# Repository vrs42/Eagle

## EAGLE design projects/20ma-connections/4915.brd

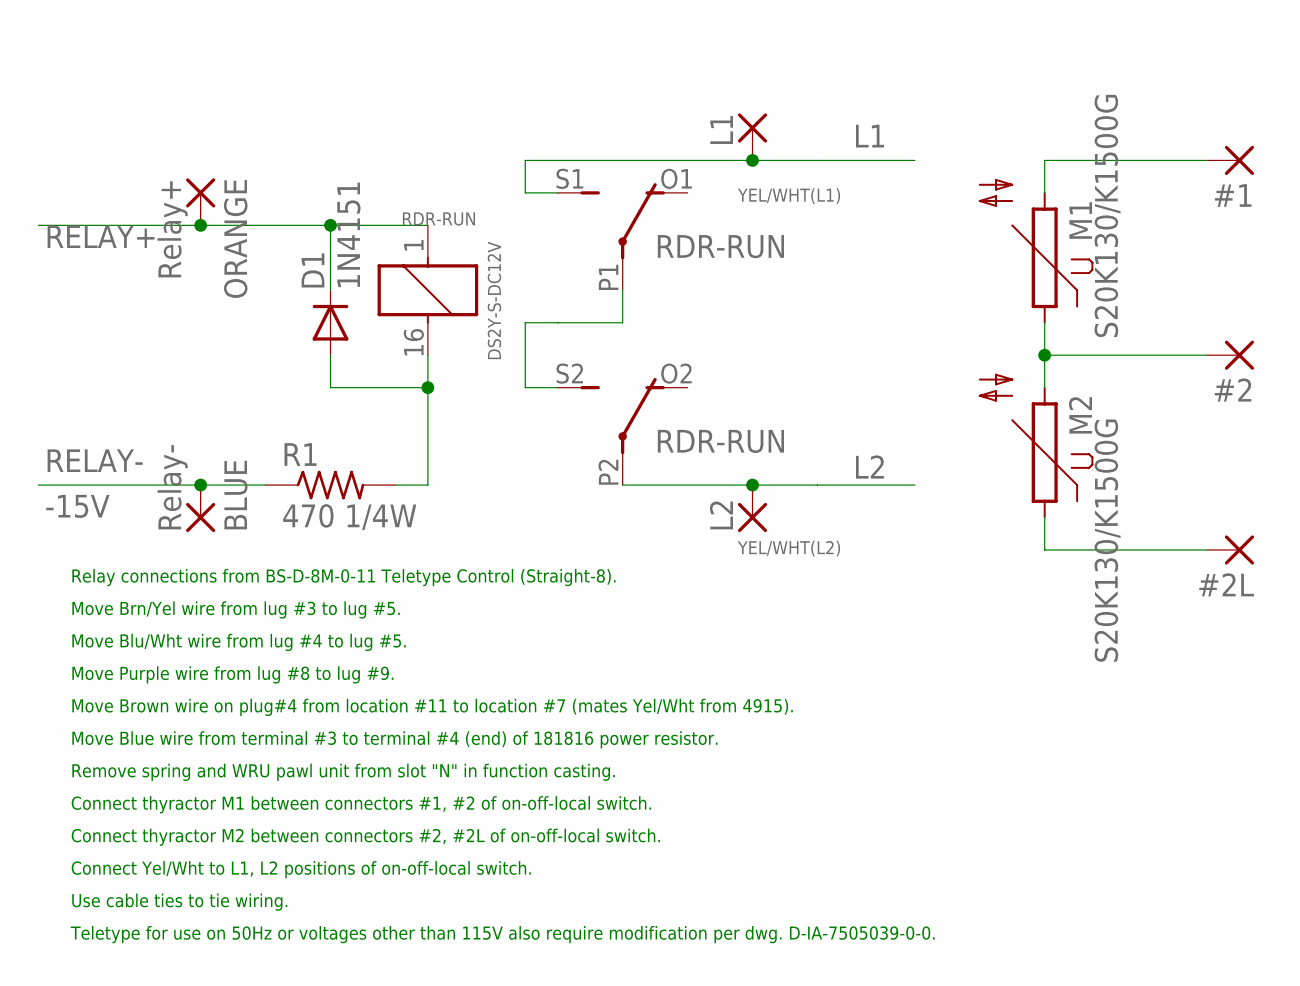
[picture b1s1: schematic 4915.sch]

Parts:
#1, #2, #2L: 2,15/1,0
BLUE: Relay-; 2,15/1,0
D1: 1N4151; DO35-10
M1, M2: S20K130/K1500G; S10K40
ORANGE: Relay+; 2,15/1,0
R1: 470 1/4W; 0309/12
RDR-RUN: DS2Y-S-DC12V; 351
YEL/WHT(L1): L1; 2,15/1,0
YEL/WHT(L2): L2; 2,15/1,0

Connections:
-15V: BLUE.1, R1.1
L1: RDR-RUN.S1 (S), YEL/WHT(L1).1
L2: RDR-RUN.P2, YEL/WHT(L2).1
unnamed: D1.A, R1.2, RDR-RUN.16 (2)
unnamed: RDR-RUN.P1, RDR-RUN.S2 (S)
unnamed: #1.1, M1.2
unnamed: #2.1, M1.1, M2.2
unnamed: #2L.1, M2.1
RELAY+: D1.C, ORANGE.1, RDR-RUN.1

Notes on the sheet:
RELAY-
Relay connections from BS-D-8M-0-11 Teletype Control (Straight-8).
Move Brown wire on plug#4 from location #11 to location #7 (mates Yel/Wht from 4915).
Move Brn/Yel wire from lug #3 to lug #5.
Move Blu/Wht wire from lug #4 to lug #5.
Move Purple wire from lug #8 to lug #9.
Move Blue wire from terminal #3 to terminal #4 (end) of 181816 power resistor.
Connect thyractor M2 between connectors #2, #2L of on-off-local switch.
Connect thyractor M1 between connectors #1, #2 of on-off-local switch.
Remove spring and WRU pawl unit from slot "N" in function casting.
Connect Yel/Wht to L1, L2 positions of on-off-local switch.
Use cable ties to tie wiring.
Teletype for use on 50Hz or voltages other than 115V also require modification per dwg. D-IA-7505039-0-0.

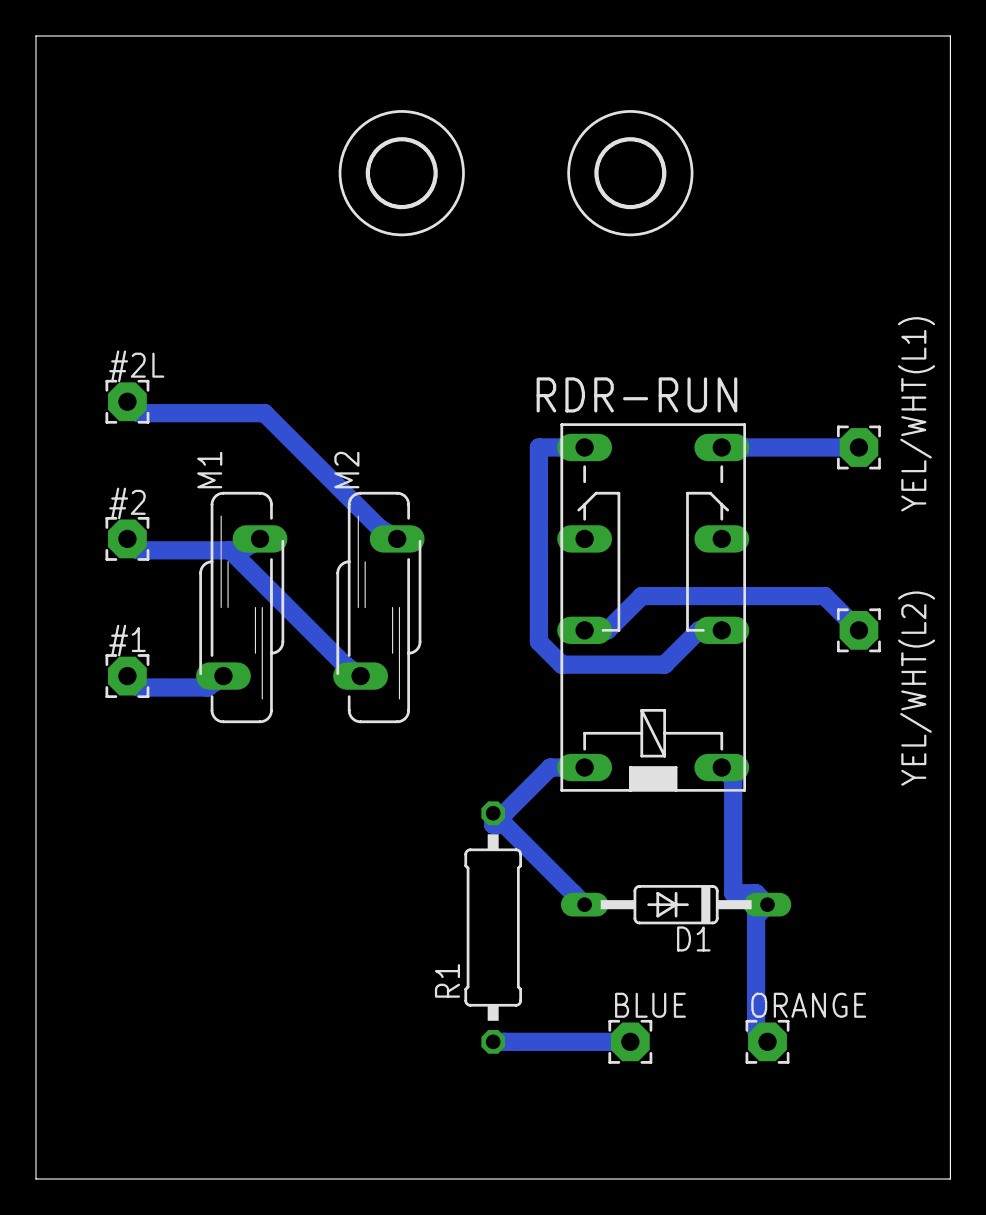
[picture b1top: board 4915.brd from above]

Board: 2 copper layers, 50.8 x 63.5 mm, 14 parts (0 on the bottom side), 9 nets.

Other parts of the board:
U$1, U$2: 3,6

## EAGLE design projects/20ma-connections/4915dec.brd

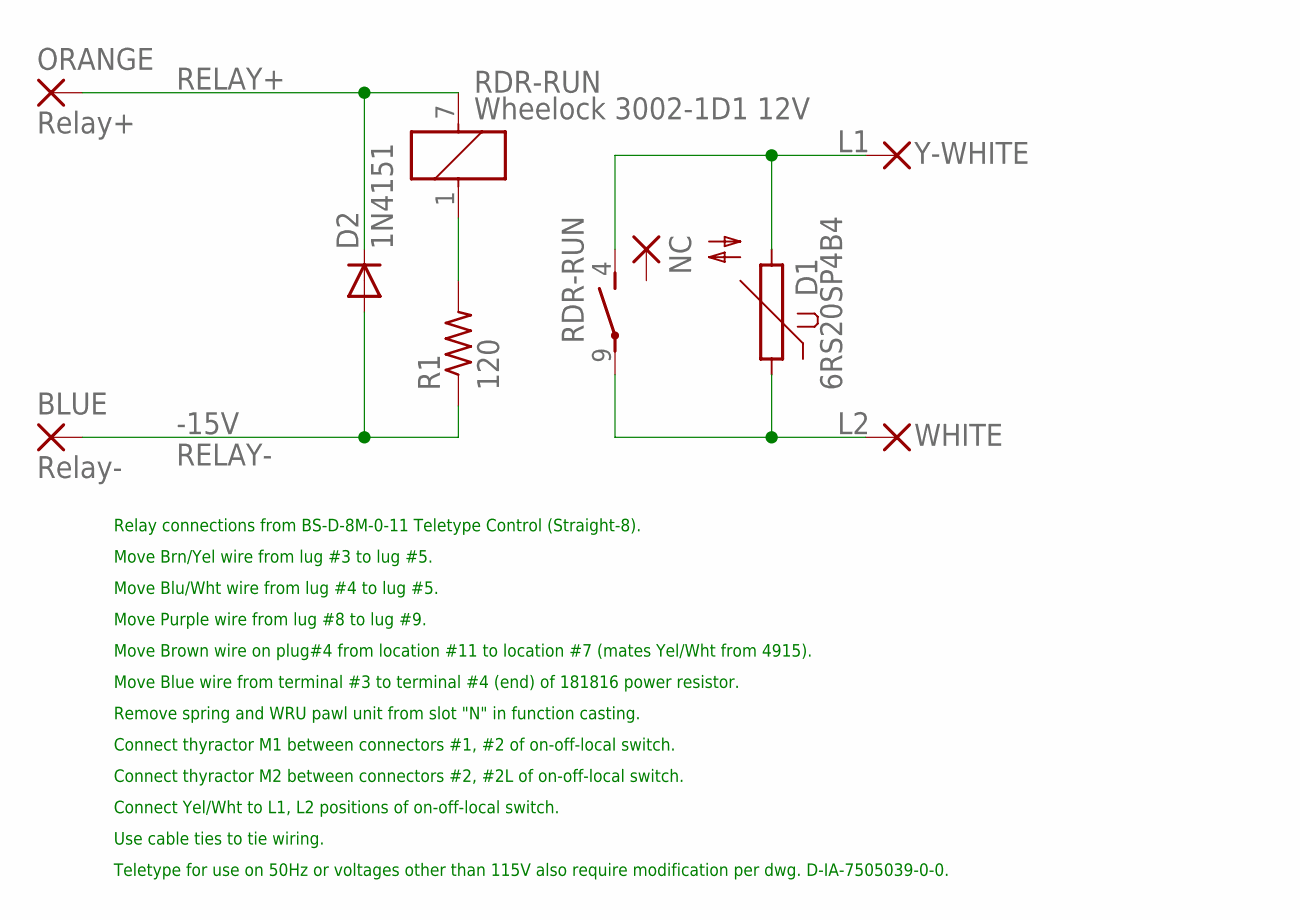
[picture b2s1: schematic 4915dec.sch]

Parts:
BLUE: Relay-; 3,17/1,3
D1: 6RS20SP4B4
D2: 1N4151; DO35-10
NC: 3,17/1,3
ORANGE: Relay+; 3,17/1,3
R1: 120; 0207/10
RDR-RUN: Wheelock 3002-1D1 12V; 3002-1D1
WHITE: L2; 3,17/1,3
Y-WHITE: L1; 3,17/1,3

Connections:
-15V: BLUE.1, D2.A, R1.1
L1: D1.2, RDR-RUN.4, Y-WHITE.1
L2: D1.1, RDR-RUN.9, WHITE.1
unnamed: R1.2, RDR-RUN.1
RELAY+: D2.C, ORANGE.1, RDR-RUN.7

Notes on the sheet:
RELAY-
Relay connections from BS-D-8M-0-11 Teletype Control (Straight-8).
Move Brown wire on plug#4 from location #11 to location #7 (mates Yel/Wht from 4915).
Move Brn/Yel wire from lug #3 to lug #5.
Move Blu/Wht wire from lug #4 to lug #5.
Move Purple wire from lug #8 to lug #9.
Move Blue wire from terminal #3 to terminal #4 (end) of 181816 power resistor.
Connect thyractor M2 between connectors #2, #2L of on-off-local switch.
Connect thyractor M1 between connectors #1, #2 of on-off-local switch.
Remove spring and WRU pawl unit from slot "N" in function casting.
Connect Yel/Wht to L1, L2 positions of on-off-local switch.
Use cable ties to tie wiring.
Teletype for use on 50Hz or voltages other than 115V also require modification per dwg. D-IA-7505039-0-0.

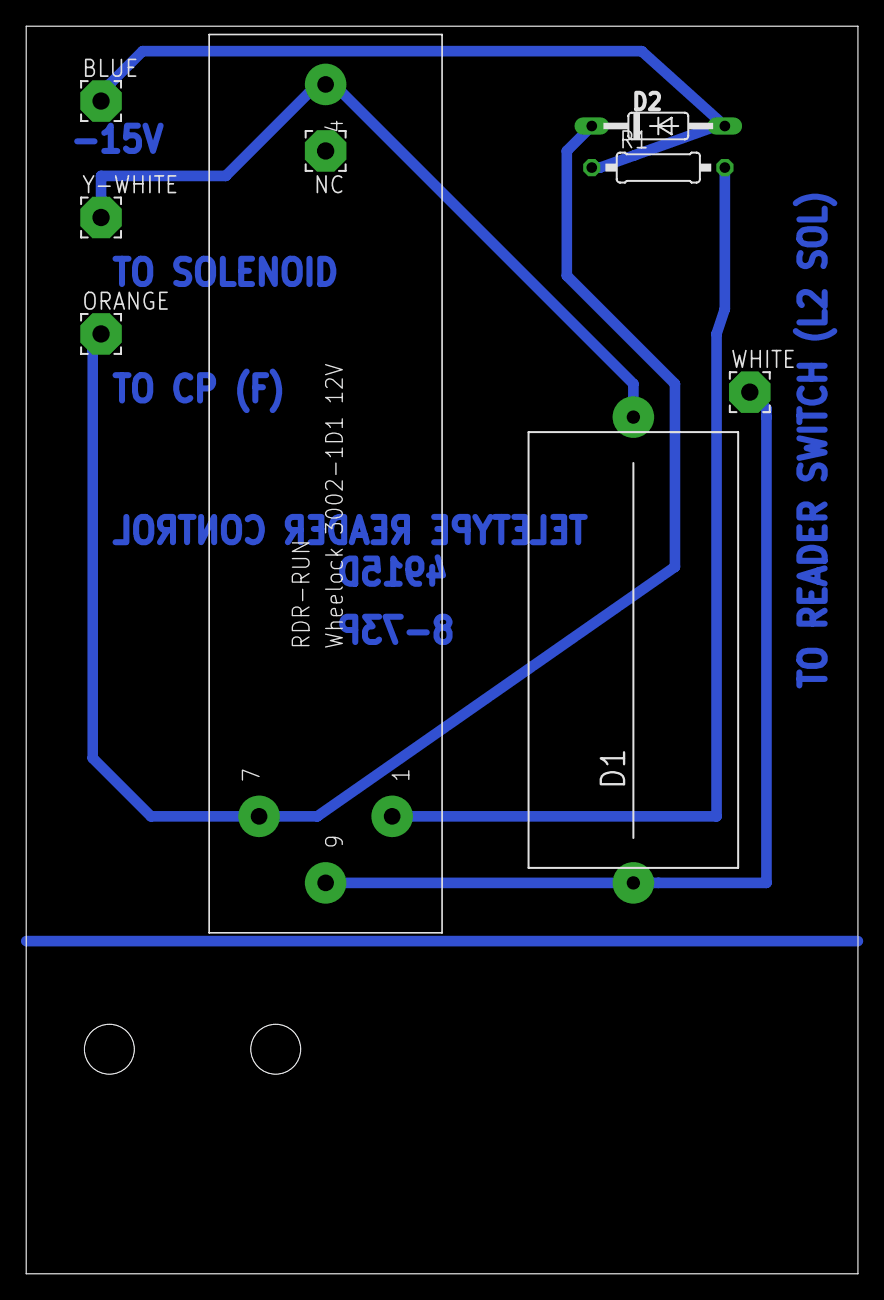
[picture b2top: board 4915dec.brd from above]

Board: 2 copper layers, 63.5 x 95.2 mm, 9 parts (0 on the bottom side), 5 nets.

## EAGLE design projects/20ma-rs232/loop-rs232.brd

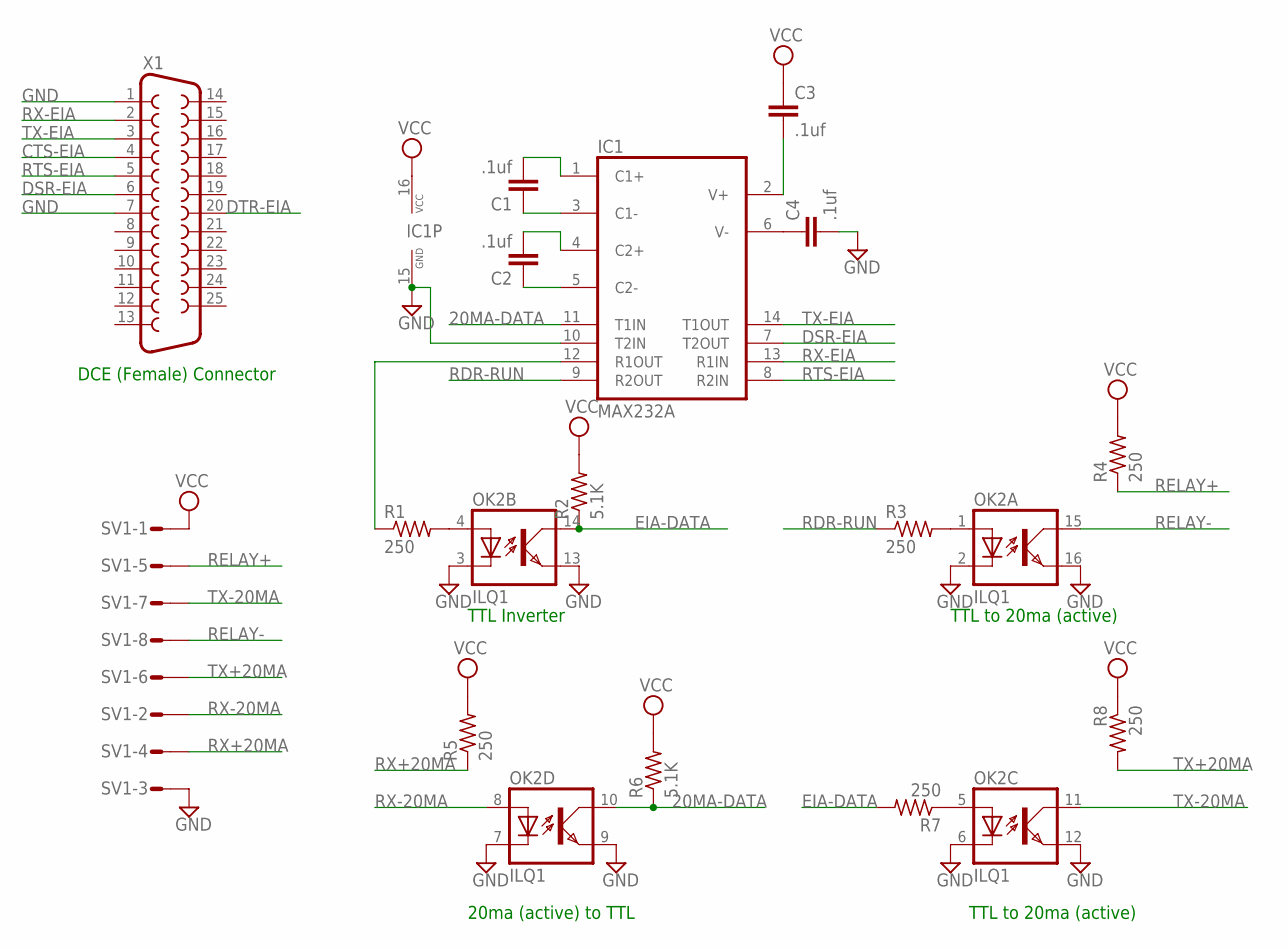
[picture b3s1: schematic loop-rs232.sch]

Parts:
C1, C2, C3, C4: .1uf; C050-025X075
IC1: MAX232A; DIL16
OK2: ILQ1; DIL16
R1, R3, R4, R5, R7, R8: 250; 0207/10
R2, R6: 5.1K; 0207/10
SV1: S08P
X1: F25H

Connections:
20MA-DATA: IC1.11 (T1IN), OK2.10 (COL), R6.1
CTS-EIA: X1.4
DSR-EIA: IC1.7 (T2OUT), X1.6
DTR-EIA: X1.20
EIA-DATA: OK2.14 (COL), R2.1, R7.2
GND: C4.2, IC1.10 (T2IN), IC1.15 (GND), OK2.2 (C), OK2.3 (C), OK2.6 (C), OK2.7 (C), OK2.9 (EMIT), OK2.12 (EMIT), OK2.13 (EMIT), OK2.16 (EMIT), SV1.3, X1.1, X1.7
unnamed: C2.1, IC1.5 (C2-)
unnamed: C2.2, IC1.4 (C2+)
unnamed: C1.2, IC1.1 (C1+)
unnamed: C1.1, IC1.3 (C1-)
unnamed: IC1.12 (R1OUT), R1.1
unnamed: C3.2, IC1.2 (V+)
unnamed: C4.1, IC1.6 (V-)
unnamed: OK2.4 (A), R1.2
unnamed: OK2.1 (A), R3.2
unnamed: OK2.5 (A), R7.1
RDR-RUN: IC1.9 (R2OUT), R3.1
RELAY+: R4.1, SV1.5
RELAY-: OK2.15 (COL), SV1.8
RTS-EIA: IC1.8 (R2IN), X1.5
RX+20MA: R5.1, SV1.4
RX-20MA: OK2.8 (A), SV1.2
RX-EIA: IC1.13 (R1IN), X1.2
TX+20MA: R8.2, SV1.6
TX-20MA: OK2.11 (COL), SV1.7
TX-EIA: IC1.14 (T1OUT), X1.3
VCC: C3.1, IC1.16 (VCC), R2.2, R4.2, R5.2, R6.2, R8.1, SV1.1

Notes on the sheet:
TTL to 20ma (active)
20ma (active) to TTL
TTL Inverter
DCE (Female) Connector

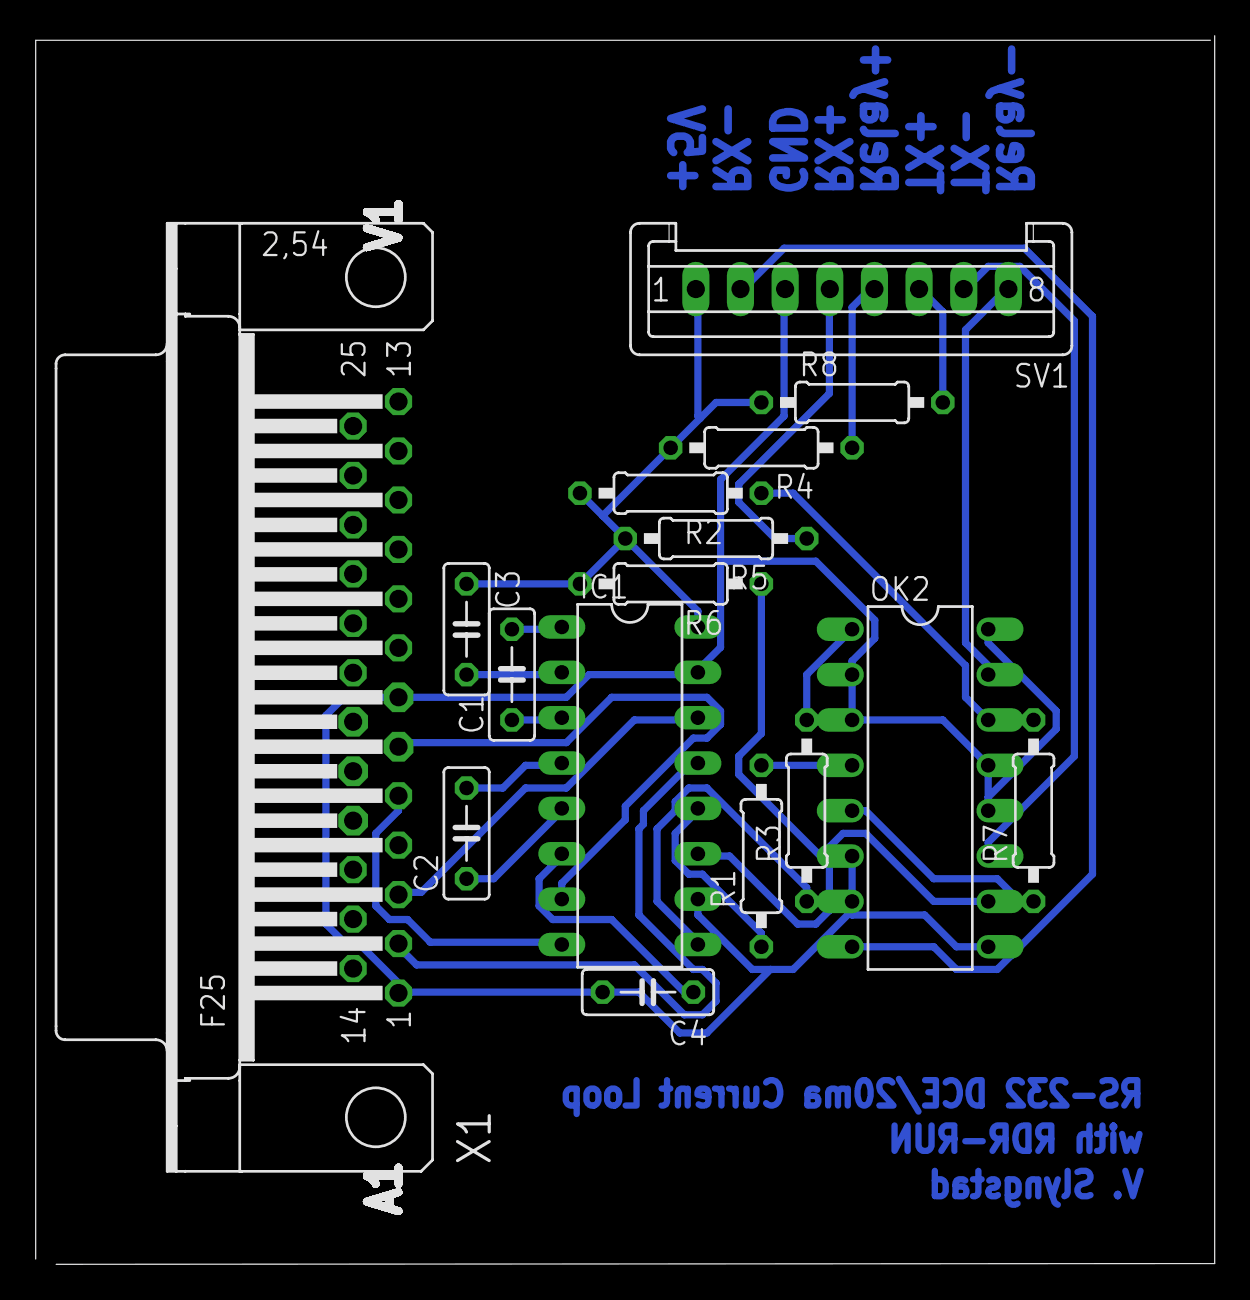
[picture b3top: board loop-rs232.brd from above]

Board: 2 copper layers, 66.0 x 68.8 mm, 16 parts (0 on the bottom side), 25 nets.

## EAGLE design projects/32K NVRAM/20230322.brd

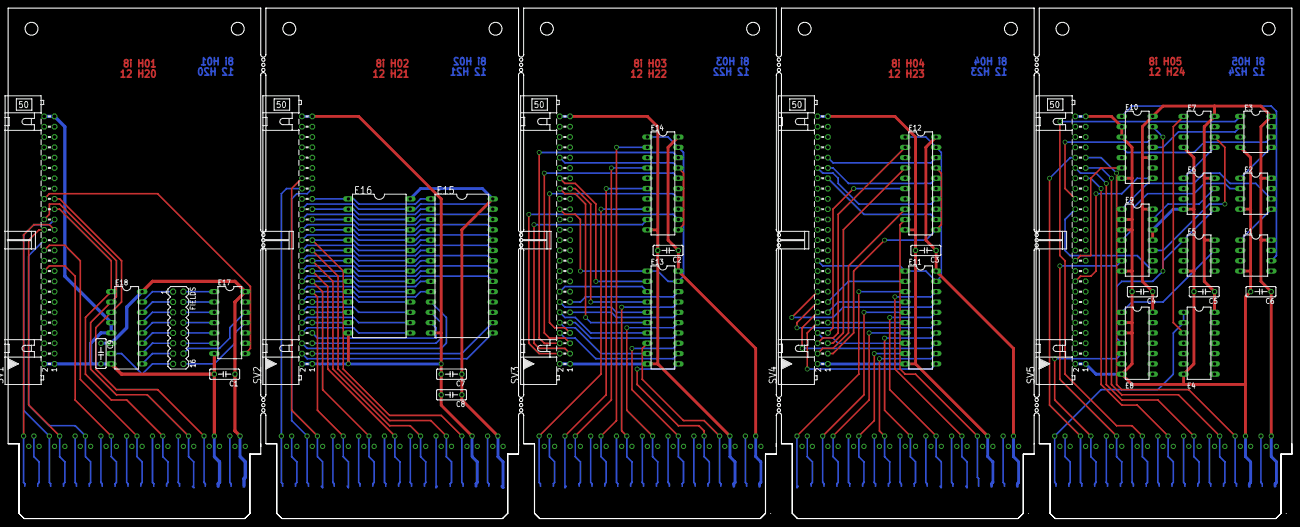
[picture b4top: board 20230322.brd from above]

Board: 2 copper layers, 316.2 x 125.7 mm, 44 parts (0 on the bottom side), 128 nets.

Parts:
C1, C2, C3, C4, C5, C6, C7, C8, C9: 0.1uF; C050-025X075
E1, E2, E3, E5, E6, E7: MXD1000; DIL08
E4: 74LS00N; DIL14
E8, E9, E10: 74LS74N; DIL14
E11, E12: 74S244N; DIL20
E13, E14: 74S240N; DIL20
E15, E16: DS1230; DIL28-6
E17: 74LS30N; DIL14
E18: 74LS138N; DIL16
FIELDS: 7 6 5 4 3 2 1 0; MA08-2
H01, H02, H03, H04, H05: EDGE-CON1
SV1, SV2, SV3, SV4, SV5: ML50L
U$1, U$2, U$3, U$4, U$5: THRU-HOLE2; THRU-HOLEB
U$6: DECPROTO11111

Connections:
BMA00(1): E15.23, E16.23, H01.K2, SV1.24, SV2.24, U$1.K2
BMA01(1): E15.21, E16.21, H01.M2, SV1.20, SV2.20, U$1.M2
BMA02(1): E15.24, E16.24, H01.P2, SV1.26, SV2.26, U$1.P2
BMA03(1): E15.25, E16.25, H01.S2, SV1.28, SV2.28, U$1.S2
BMA04(1): E15.3, E16.3, H01.T2, SV1.29, SV2.29, U$1.T2
BMA05(1): E15.4, E16.4, H01.V2, SV1.27, SV2.27, U$1.V2
BMA06(1): E15.5, E16.5, H02.D2, SV2.25, U$2.D2
BMA07(1): E15.6, E16.6, H02.E2, SV2.23, U$2.E2
BMA08(1): E15.7, E16.7, H02.H2, SV2.21, U$2.H2
BMA09(1): E15.8, E16.8, H02.K2, SV2.19, U$2.K2
BMA10(1): E15.9, E16.9, H02.M2, SV2.17, U$2.M2
BMA11(1): E15.10, E16.10, H02.P2, SV2.15, U$2.P2
BTP2(0): E4.3, E7.1
BTP2(1): E4.1, E4.2, H05.V2, U$5.V2
CS(0): E10.8, E15.20, E16.20, SV2.18, SV5.18
D0: E11.2, E13.18, E16.11, SV2.13, SV3.13, SV4.13
D1: E11.4, E13.16, E16.12, SV2.11, SV3.11, SV4.11
D2: E11.6, E13.14, E16.13, SV2.9, SV3.9, SV4.9
D3: E11.8, E13.12, E16.15, SV2.8, SV3.8, SV4.8
D4: E11.11, E13.9, E16.16, SV2.10, SV3.10, SV4.10
D5: E11.13, E13.7, E16.17, SV2.12, SV3.12, SV4.12
D6: E11.15, E13.5, E16.18, SV2.14, SV3.14, SV4.14
D7: E11.17, E13.3, E16.19, SV2.16, SV3.16, SV4.16
D8: E12.2, E14.18, E15.11, SV2.6, SV3.6, SV4.6
D9: E12.4, E14.16, E15.12, SV2.5, SV3.5, SV4.5
D10: E12.6, E14.14, E15.13, SV2.7, SV3.7, SV4.7
D11: E12.8, E14.12, E15.15, SV2.4, SV3.4, SV4.4
EA0(1): E15.1, E16.1, E18.3, H01.D2, SV1.33, SV2.33, U$1.D2
EA1(1): E15.26, E16.26, E18.2, H01.E2, SV1.30, SV2.30, U$1.E2
EA2(1): E15.2, E16.2, E18.1, H01.H2, SV1.31, SV2.31, U$1.H2
FS(1): E10.12, E17.8, SV1.34, SV5.34
GND: C1.2, C2.2, C3.2, C4.2, C5.2, C6.2, C7.2, C8.2, C9.2, E1.4, E2.4, E3.4, E4.7, E5.4, E6.4, E7.4, E8.2, E8.3, E8.7, E9.2, E9.3, E9.7, E9.11, E9.12, E10.2, E10.3, E10.7, E11.10, E12.10, E13.10, E14.10, E15.14, E16.14, E17.7, E18.4, E18.5, E18.8, H01.C2, H02.C2, H03.C2, H04.C2, H05.C2, SV1.1, SV1.2, SV1.49, SV1.50, SV2.1, SV2.2, SV2.49, SV2.50, SV3.1, SV3.2, SV3.49, SV3.50, SV4.1, SV4.2, SV4.49, SV4.50, SV5.1, SV5.2, SV5.49, SV5.50, U$1.C2, U$2.C2, U$3.C2, U$4.C2, U$5.C2
MBODD_P: E14.11, E14.13, E14.15, E14.17, H05.T2, SV3.42, SV5.42, U$5.T2
MCBMB00(0): E13.2, H02.S2, SV2.38, SV3.38, U$2.S2
MCBMB01(0): E13.4, H02.T2, SV2.35, SV3.35, U$2.T2
MCBMB02(0): E13.6, H02.V2, SV2.36, SV3.36, U$2.V2
MCBMB03(0): E13.8, H03.D2, U$3.D2
MCBMB04(0): E13.11, H03.E2, U$3.E2
MCBMB05(0): E13.13, H03.H2, U$3.H2
MCBMB06(0): E13.15, H03.K2, U$3.K2
MCBMB07(0): E13.17, H03.M2, U$3.M2
MCBMB08(0): E14.2, H03.P2, U$3.P2
MCBMB09(0): E14.4, H03.S2, U$3.S2
MCBMB10(0): E14.6, H03.T2, U$3.T2
MCBMB11(0): E14.8, H03.V2, U$3.V2
MEM00: E11.18, H04.E2, U$4.E2
MEM01: E11.16, H04.H2, U$4.H2
MEM02: E11.14, H04.K2, U$4.K2
MEM03: E11.12, H04.M2, U$4.M2
MEM04: E11.9, H04.P2, U$4.P2
MEM05: E11.7, H04.S2, U$4.S2
MEM06: E11.5, H04.T2, U$4.T2
MEM07: E11.3, H04.V2, U$4.V2
MEM08: E12.18, H05.D2, SV4.41, SV5.41, U$5.D2
MEM09: E12.16, H05.E2, SV4.39, SV5.39, U$5.E2
MEM10: E12.14, H05.H2, SV4.40, SV5.40, U$5.H2
MEM11: E12.12, H05.K2, SV4.37, SV5.37, U$5.K2
MEMDONE(1): E8.5, H05.S2, U$5.S2
MEMSTART(0): E3.1, H05.M2, U$5.M2
MEM_P: E12.9, H04.D2, U$4.D2
MS100: E3.2, E10.11
MS150: E3.6, E10.4
MS250: E2.1, E3.5
MS350: E2.2, E9.4
MS400: E2.6, E9.1
MS500: E1.1, E2.5
MS650: E1.6, E10.1
unnamed: H01.L2, U$1.L2
unnamed: H01.N2, U$1.N2
unnamed: H01.R2, U$1.R2
unnamed: H02.L2, U$2.L2
unnamed: H02.N2, U$2.N2
unnamed: H01.J2, U$1.J2
unnamed: H02.R2, U$2.R2
unnamed: H01.F2, U$1.F2
unnamed: H02.J2, U$2.J2
unnamed: H02.F2, U$2.F2
unnamed: H02.U2, U$2.U2
unnamed: H01.U2, U$1.U2
unnamed: H02.B2, U$2.B2
unnamed: H01.B2, U$1.B2
unnamed: E18.15, FIELDS.1
unnamed: E18.14, FIELDS.3
unnamed: E18.13, FIELDS.5
unnamed: E18.12, FIELDS.7
unnamed: E18.11, FIELDS.9
unnamed: E18.10, FIELDS.11
unnamed: E18.9, FIELDS.13
unnamed: E18.7, FIELDS.15
unnamed: E17.4, FIELDS.8
unnamed: E17.3, FIELDS.6
unnamed: E17.2, FIELDS.4
unnamed: E17.1, FIELDS.2
unnamed: E17.5, FIELDS.10
unnamed: E17.6, FIELDS.12
unnamed: E17.12, FIELDS.14
unnamed: E17.11, FIELDS.16
unnamed: H04.J2, U$4.J2
unnamed: H04.L2, U$4.L2
unnamed: H04.N2, U$4.N2
unnamed: H03.J2, U$3.J2
unnamed: H03.L2, U$3.L2
unnamed: H03.N2, U$3.N2
unnamed: H03.F2, U$3.F2
unnamed: H03.R2, U$3.R2
unnamed: H03.B2, U$3.B2
unnamed: H03.U2, U$3.U2
unnamed: H05.J2, U$5.J2
unnamed: H05.L2, U$5.L2
unnamed: H05.N2, U$5.N2
unnamed: H05.F2, U$5.F2
unnamed: H05.R2, U$5.R2
unnamed: H05.B2, U$5.B2
unnamed: H05.U2, U$5.U2
unnamed: H04.F2, U$4.F2
unnamed: H04.R2, U$4.R2
unnamed: H04.B2, U$4.B2
unnamed: H04.U2, U$4.U2
OE(0): E10.6, E11.1, E11.19, E12.1, E12.19, E15.22, E16.22, SV2.22, SV4.22, SV5.22
PARITY: E12.11, E12.13, E12.15, E12.17, E14.9, E15.16, SV2.3, SV3.3, SV4.3
STROBE(0): E9.6, H05.P2, U$5.P2
TP150: E7.6, E9.10
TP250: E6.1, E7.5
TP300: E6.7, E9.13
TP500: E5.1, E6.5, E8.4, E10.13
TP550: E5.7, E8.1
VCC: C1.1, C2.1, C3.1, C4.1, C5.1, C6.1, C7.1, C8.1, C9.1, E1.8, E2.8, E3.8, E4.14, E5.8, E6.8, E7.8, E8.14, E9.14, E10.10, E10.14, E11.20, E12.20, E13.20, E14.20, E15.28, E16.28, E17.14, E18.6, E18.16, H01.A2, H02.A2, H03.A2, H04.A2, H05.A2, U$1.A2, U$2.A2, U$3.A2, U$4.A2, U$5.A2
WE(0): E9.8, E13.1, E13.19, E14.1, E14.19, E15.27, E16.27, SV2.32, SV3.32, SV5.32

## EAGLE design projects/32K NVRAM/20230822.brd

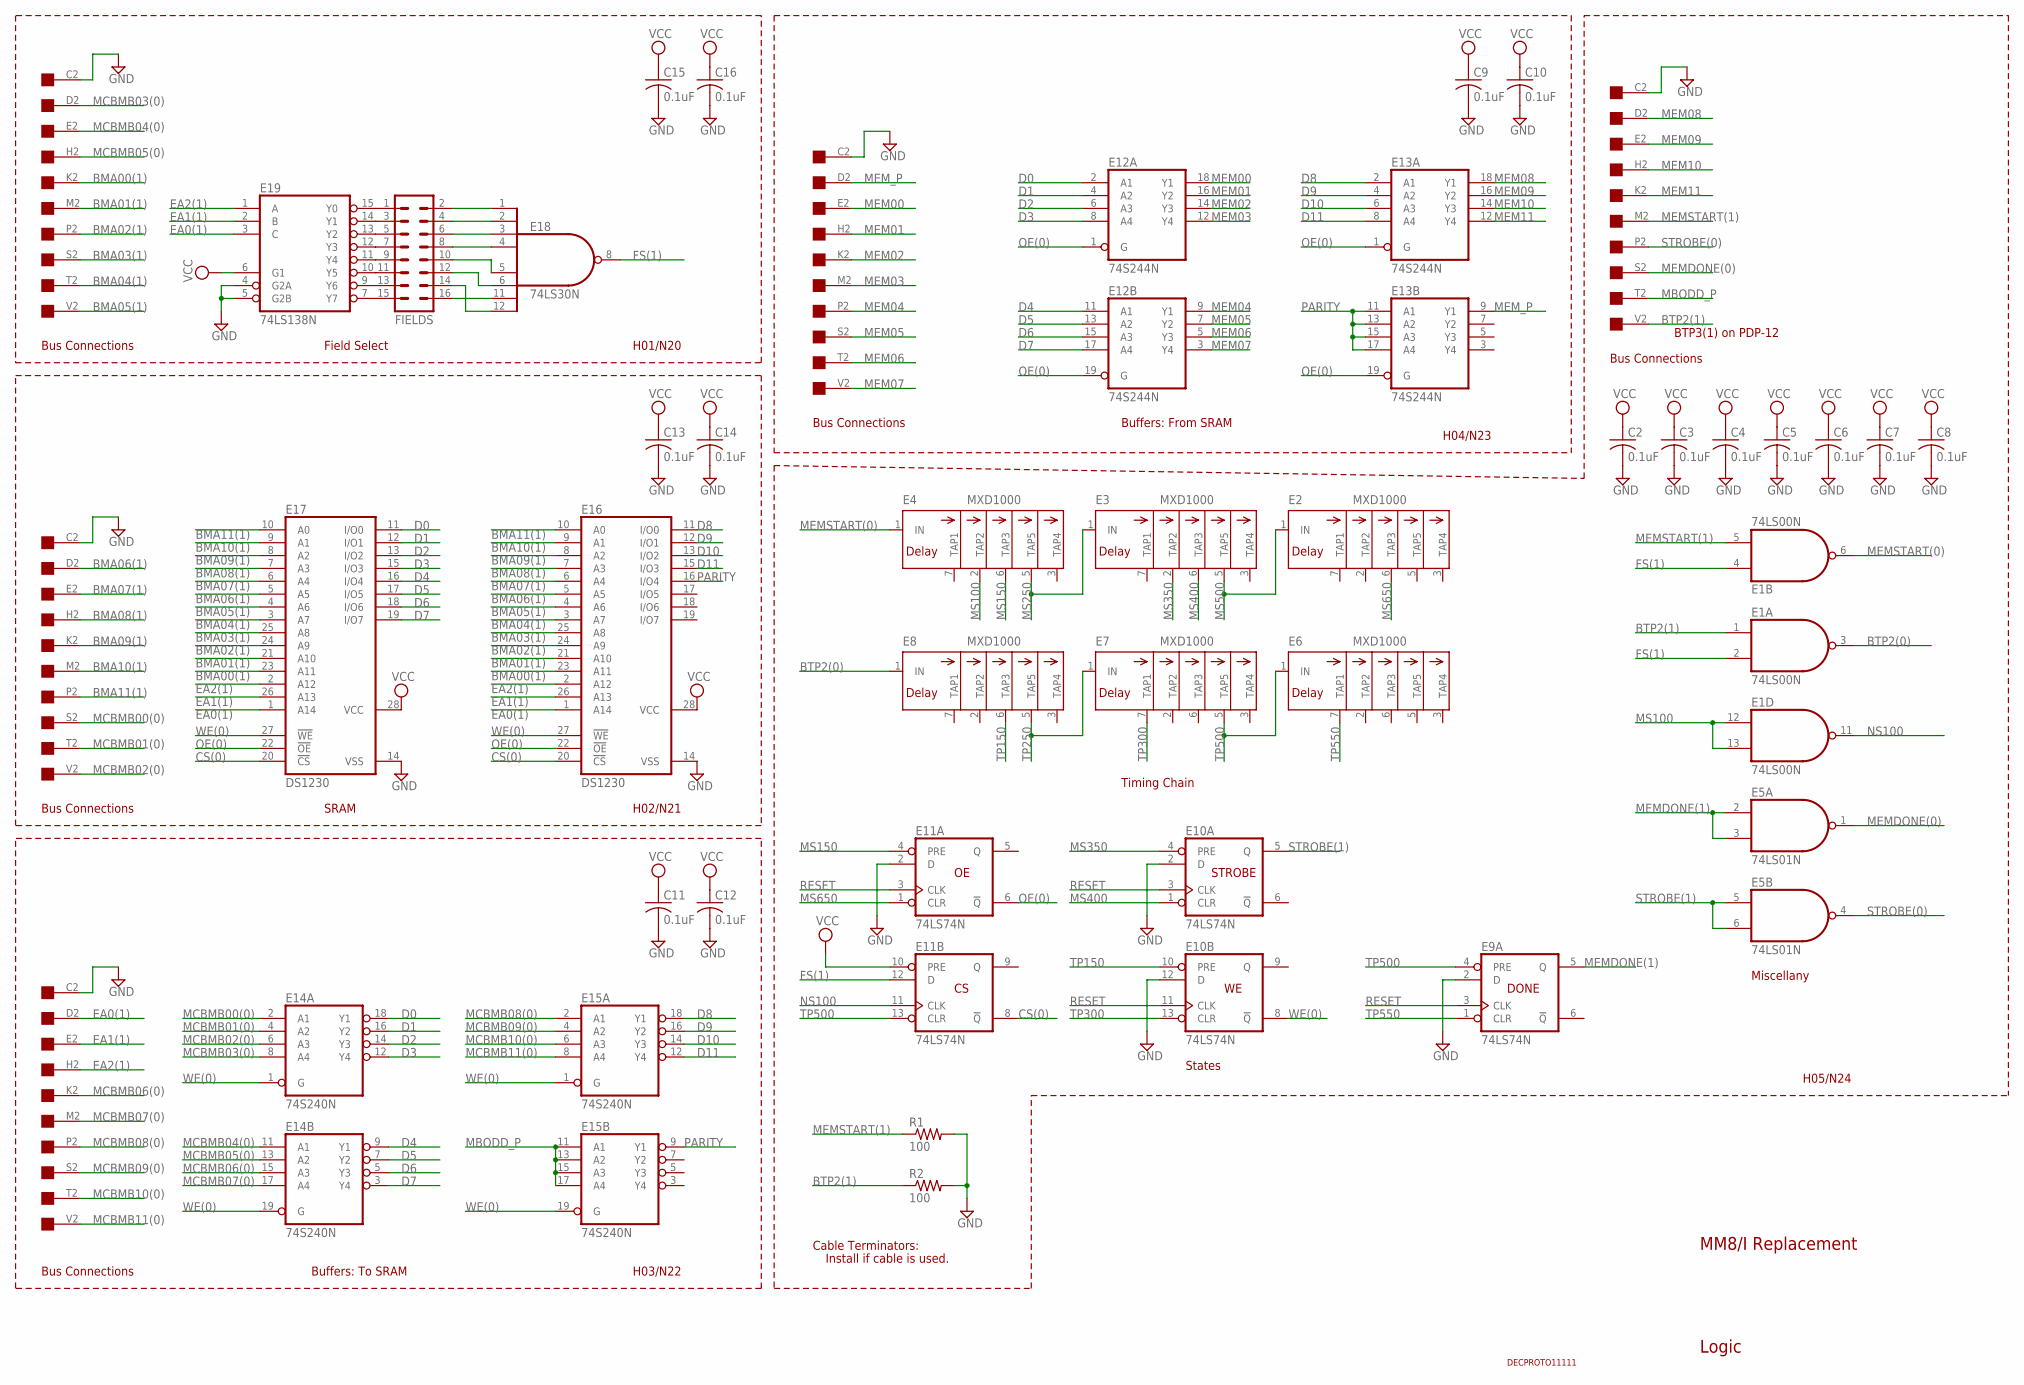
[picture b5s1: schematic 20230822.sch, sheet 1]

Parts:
C2, C3, C4, C5, C6, C7, C8, C9, C10, C11, C12, C13, C14, C15, C16: 0.1uF; C050-025X075
E1: 74LS00N; DIL14
E2, E3, E4, E6, E7, E8: MXD1000; DIL08
E5: 74LS01N; DIL14
E9, E10, E11: 74LS74N; DIL14
E12, E13: 74S244N; DIL20
E14, E15: 74S240N; DIL20
E16, E17: DS1230; DIL28-6
E18: 74LS30N; DIL14
E19: 74LS138N; DIL16
FIELDS: MA08-2
H01, H02, H03, H04, H05: EDGE-CON1
R1, R2: 100; 0207/10
U$6: DECPROTO11111

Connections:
BMA00(1): E16.23 (A11), E17.23 (A11), H01.K2; also elsewhere on the board
BMA01(1): E16.21 (A10), E17.21 (A10), H01.M2; also elsewhere on the board
BMA02(1): E16.24 (A9), E17.24 (A9), H01.P2; also elsewhere on the board
BMA03(1): E16.25 (A8), E17.25 (A8), H01.S2; also elsewhere on the board
BMA04(1): E16.3 (A7), E17.3 (A7), H01.T2; also elsewhere on the board
BMA05(1): E16.4 (A6), E17.4 (A6), H01.V2; also elsewhere on the board
BMA06(1): E16.5 (A5), E17.5 (A5), H02.D2; also elsewhere on the board
BMA07(1): E16.6 (A4), E17.6 (A4), H02.E2; also elsewhere on the board
BMA08(1): E16.7 (A3), E17.7 (A3), H02.H2; also elsewhere on the board
BMA09(1): E16.8 (A2), E17.8 (A2), H02.K2; also elsewhere on the board
BMA10(1): E16.9 (A1), E17.9 (A1), H02.M2; also elsewhere on the board
BMA11(1): E16.10 (A0), E17.10 (A0), H02.P2; also elsewhere on the board
BTP2(0): E1.3 (O), E8.1 (IN)
BTP2(1): E1.1 (I0), H05.V2, R2.1
CS(0): E11.8 (!Q), E16.20 (!CS), E17.20 (!CS); also elsewhere on the board
D0: E12.2 (A1), E14.18 (Y1), E17.11 (I/O0); also elsewhere on the board
D1: E12.4 (A2), E14.16 (Y2), E17.12 (I/O1); also elsewhere on the board
D2: E12.6 (A3), E14.14 (Y3), E17.13 (I/O2); also elsewhere on the board
D3: E12.8 (A4), E14.12 (Y4), E17.15 (I/O3); also elsewhere on the board
D4: E12.11 (A1), E14.9 (Y1), E17.16 (I/O4); also elsewhere on the board
D5: E12.13 (A2), E14.7 (Y2), E17.17 (I/O5); also elsewhere on the board
D6: E12.15 (A3), E14.5 (Y3), E17.18 (I/O6); also elsewhere on the board
D7: E12.17 (A4), E14.3 (Y4), E17.19 (I/O7); also elsewhere on the board
D8: E13.2 (A1), E15.18 (Y1), E16.11 (I/O0); also elsewhere on the board
D9: E13.4 (A2), E15.16 (Y2), E16.12 (I/O1); also elsewhere on the board
D10: E13.6 (A3), E15.14 (Y3), E16.13 (I/O2); also elsewhere on the board
D11: E13.8 (A4), E15.12 (Y4), E16.15 (I/O3); also elsewhere on the board
EA0(1): E16.1 (A14), E17.1 (A14), E19.3 (C), H03.D2; also elsewhere on the board
EA1(1): E16.26 (A13), E17.26 (A13), E19.2 (B), H03.E2; also elsewhere on the board
EA2(1): E16.2 (A12), E17.2 (A12), E19.1 (A), H03.H2; also elsewhere on the board
FS(1): E1.2 (I1), E1.4 (I0), E11.12 (D), E18.8 (O); also elsewhere on the board
GND: C2.2, C3.2, C4.2, C5.2, C6.2, C7.2, C8.2, C9.2, C10.2, C11.2, C12.2, C13.2, C14.2, C15.2, C16.2, E1.7 (GND), E2.4 (GND), E3.4 (GND), E4.4 (GND), E5.7 (GND), E6.4 (GND), E7.4 (GND), E8.4 (GND), E9.2 (D), E9.7 (GND), E10.2 (D), E10.7 (GND), E10.12 (D), E11.2 (D), E11.7 (GND), E12.10 (GND), E13.10 (GND), E14.10 (GND), E15.10 (GND), E16.14 (VSS), E17.14 (VSS), E18.7 (GND), E19.4 (G2A), E19.5 (G2B), E19.8 (GND), H01.C2, H02.C2, H03.C2, H04.C2, H05.C2, R1.2, R2.2; also elsewhere on the board
MBODD_P: E15.11 (A1), E15.13 (A2), E15.15 (A3), E15.17 (A4), H05.T2; also elsewhere on the board
MCBMB00(0): E14.2 (A1), H02.S2; also elsewhere on the board
MCBMB01(0): E14.4 (A2), H02.T2; also elsewhere on the board
MCBMB02(0): E14.6 (A3), H02.V2; also elsewhere on the board
MCBMB03(0): E14.8 (A4), H01.D2; also elsewhere on the board
MCBMB04(0): E14.11 (A1), H01.E2; also elsewhere on the board
MCBMB05(0): E14.13 (A2), H01.H2; also elsewhere on the board
MCBMB06(0): E14.15 (A3), H03.K2
MCBMB07(0): E14.17 (A4), H03.M2
MCBMB08(0): E15.2 (A1), H03.P2
MCBMB09(0): E15.4 (A2), H03.S2
MCBMB10(0): E15.6 (A3), H03.T2
MCBMB11(0): E15.8 (A4), H03.V2
MEM00: E12.18 (Y1), H04.E2
MEM01: E12.16 (Y2), H04.H2
MEM02: E12.14 (Y3), H04.K2
MEM03: E12.12 (Y4), H04.M2
MEM04: E12.9 (Y1), H04.P2
MEM05: E12.7 (Y2), H04.S2
MEM06: E12.5 (Y3), H04.T2
MEM07: E12.3 (Y4), H04.V2
MEM08: E13.18 (Y1), H05.D2; also elsewhere on the board
MEM09: E13.16 (Y2), H05.E2; also elsewhere on the board
MEM10: E13.14 (Y3), H05.H2; also elsewhere on the board
MEM11: E13.12 (Y4), H05.K2; also elsewhere on the board
MEMDONE(0): E5.1 (O), H05.S2
MEMDONE(1): E5.2 (I0), E5.3 (I1), E9.5 (Q)
MEMSTART(0): E1.6 (O), E4.1 (IN); also elsewhere on the board
MEMSTART(1): E1.5 (I1), H05.M2, R1.1
MEM_P: E13.9 (Y1), H04.D2
MS100: E1.12 (I0), E1.13 (I1), E4.2 (TAP2)
MS150: E4.6 (TAP3), E11.4 (PRE)
MS250: E3.1 (IN), E4.5 (TAP5)
MS350: E3.2 (TAP2), E10.4 (PRE)
MS400: E3.6 (TAP3), E10.1 (CLR)
MS500: E2.1 (IN), E3.5 (TAP5)
MS650: E2.6 (TAP3), E11.1 (CLR)
unnamed: E19.15 (Y0), FIELDS.1
unnamed: E19.14 (Y1), FIELDS.3
unnamed: E19.13 (Y2), FIELDS.5
unnamed: E19.12 (Y3), FIELDS.7
unnamed: E19.11 (Y4), FIELDS.9
unnamed: E19.10 (Y5), FIELDS.11
unnamed: E19.9 (Y6), FIELDS.13
unnamed: E19.7 (Y7), FIELDS.15
unnamed: E18.4 (I3), FIELDS.8
unnamed: E18.3 (I2), FIELDS.6
unnamed: E18.2 (I1), FIELDS.4
unnamed: E18.1 (I0), FIELDS.2
unnamed: E18.5 (I4), FIELDS.10
unnamed: E18.6 (I5), FIELDS.12
unnamed: E18.12 (I7), FIELDS.14
unnamed: E18.11 (I6), FIELDS.16
NS100: E1.11 (O), E11.11 (CLK)
OE(0): E11.6 (!Q), E12.1 (G), E12.19 (G), E13.1 (G), E13.19 (G), E16.22 (!OE), E17.22 (!OE); also elsewhere on the board
PARITY: E13.11 (A1), E13.13 (A2), E13.15 (A3), E13.17 (A4), E15.9 (Y1), E16.16 (I/O4); also elsewhere on the board
RESET: E9.3 (CLK), E10.3 (CLK), E10.11 (CLK), E11.3 (CLK); also elsewhere on the board
STROBE(0): E5.4 (O), H05.P2
STROBE(1): E5.5 (I0), E5.6 (I1), E10.5 (Q)
TP150: E8.6 (TAP3), E10.10 (PRE)
TP250: E7.1 (IN), E8.5 (TAP5)
TP300: E7.7 (TAP1), E10.13 (CLR)
TP500: E6.1 (IN), E7.5 (TAP5), E9.4 (PRE), E11.13 (CLR)
TP550: E6.7 (TAP1), E9.1 (CLR)
VCC: C2.1, C3.1, C4.1, C5.1, C6.1, C7.1, C8.1, C9.1, C10.1, C11.1, C12.1, C13.1, C14.1, C15.1, C16.1, E1.14 (VCC), E2.8 (VCC), E3.8 (VCC), E4.8 (VCC), E5.14 (VCC), E6.8 (VCC), E7.8 (VCC), E8.8 (VCC), E9.14 (VCC), E10.14 (VCC), E11.10 (PRE), E11.14 (VCC), E12.20 (VCC), E13.20 (VCC), E14.20 (VCC), E15.20 (VCC), E16.28 (VCC), E17.28 (VCC), E18.14 (VCC), E19.6 (G1), E19.16 (VCC); also elsewhere on the board
WE(0): E10.8 (!Q), E14.1 (G), E14.19 (G), E15.1 (G), E15.19 (G), E16.27 (!WE), E17.27 (!WE); also elsewhere on the board

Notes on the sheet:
STROBE
DONE
H01/N20
H02/N21
H03/N22
H04/N23
Field Select
SRAM
MM8/I Replacement
Buffers: To SRAM
Buffers: From SRAM
Timing Chain
States
BTP3(1) on PDP-12
Miscellany
H05/N24
Logic
Bus Connections
Cable Terminators:
Install if cable is used.
